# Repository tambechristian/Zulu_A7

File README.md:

# Zulu A7

Zulu A7 is a USB FPGA board built around an AMD/Xilinx Artix-7
XC7A35T-2CPG236I. An FTDI FT2232HL bridge provides JTAG (channel A) and a
UART (channel B) over one micro-USB port. The board carries 64 MB of SDRAM,
a 128 Mbit quad-SPI configuration flash, a microSD socket, a Pmod host
header and a 40-pin breadboard header. It runs from USB through a
single-cell LiPo charger with power path and three buck regulators (3.3 V,
1.8 V and 1.0 V). The PCB is a 69.85 x 25.40 mm, six-layer HDI board.

The main design is the Altium Designer project in `Zulu_Altium_VS_Code/`.
Its fabrication and turnkey-assembly packages for PCBWay are dated
2026-10-07. Build and test results are not recorded in this repository.

## Origin and attribution

Zulu A7 is an adaptation of **XuLA2**, the USB FPGA prototyping board by
Dave Vandenbout / XESS Corp. (copyright 2012 XESS Corp.), published at
<https://github.com/xesscorp/XuLA2>. Its hardware design (schematic and
layout in `pcb/`) is licensed under
[CC BY-SA 3.0 Unported](https://creativecommons.org/licenses/by-sa/3.0/),
per the notice on its schematic. This repository does
not imply any connection with, or endorsement by, XESS Corp. or Dave
Vandenbout.

XESS's [product listing](https://www.tindie.com/products/xesscorp/xula2-lx25-fpga-prototyping-board/)
says the whole XuLA2 design was made open source and that anyone who
re-designs it must open-source their design too. As of 2026-10-07 it lists
XuLA2 as retired. The licence terms are those of CC BY-SA 3.0.

XuLA2 (schematic version 2.0, EAGLE 5 files) had a Xilinx Spartan-6
XC6SLX25 in FT256 and a Microchip PIC18F14K50 that handled reset and
initialisation, clock generation and USB-to-JTAG. It also had 256 Mbit
SDRAM, 8 Mbit SPI flash, a microSD socket, a mini-USB connector, ZLDO1117
3.3 V and 1.2 V regulators, a 40-pin breadboard prototyping header and an
aux JTAG header.

### Lineage

1. **XuLA2**: XESS Corp., 2012. The upstream design.
2. **XuLA3**: Christian Tambe's own rework of XuLA2, started 2026-08-10 in a
   separate local repository that is not published. It is not an XESS
   design. Its baseline is the XuLA2 schematic in EAGLE XML. The move to the
   Artix-7, the FT2232H bridge and an LTC3569 triple buck was made in XuLA3,
   before the fork. There the `xess` library was renamed `ctambe`, and the
   schematic AUTHOR and copyright line were changed to Christian Tambe.
3. **Zulu A7**: forked from XuLA3 on 2026-08-29 (commit `30a0e65`, "Zulu A7
   forks from XuLA3: the board is renamed, not redesigned"). That commit
   renamed X2's package XULA-DIP37 to ZULU-DIP37 and its deviceset XULA-CONN
   to ZULU-CONN, dropped unused devicesets including XC6SLX25-FT256 and
   PIC18F14K50, and set the version to 1.0. `zulu_a7.brd` took only its
   layer, settings and autorouter sections from the XuLA3 board;
   `tools/make_board.py` writes the geometry new.
4. **Altium and KiCad copies**: the EAGLE schematic was imported into Altium
   with the EAGLE Import Wizard in `Zulu_Altrium/` (commit `6d2efd6`).
   `Zulu_Altium_VS_Code/` is a later working copy of that project. The SC189
   regulators, the BQ24232 charger and the X2 pin field are Altium-side
   changes, and the board was routed there. `Zulu_kicad/` is a KiCad
   conversion of the Altium project.

### Main changes from XuLA2

| | XuLA2 | Zulu A7 |
|---|---|---|
| FPGA | Xilinx Spartan-6 XC6SLX25, FT256 | AMD/Xilinx Artix-7 XC7A35T-2CPG236I |
| USB bridge | Microchip PIC18F14K50 | FTDI FT2232HL with a 93LC46B EEPROM |
| USB connector | Hirose UX60SC-MB-5ST mini-USB | Molex 105017-0001 micro-USB |
| SDRAM | W9825G6JH-5, 256 Mbit | Alliance AS4C32M16SB-7TCN, 512 Mbit |
| Flash | W25Q80BV, 8 Mbit | Winbond W25Q128JV, 128 Mbit quad SPI |
| microSD | ALPS SCHD3A0100 | Hirose DM3D-SF |
| Clock | generated by the PIC18F14K50 | 12.000 MHz oscillator shared by the FT2232HL and the FPGA |
| Power | ZLDO1117 3.3 V and 1.2 V regulators | BQ24232 LiPo charger and three SC189 bucks (3.3 / 1.8 / 1.0 V) |
| Headers | 40-pin breadboard header, aux JTAG header | 40-pin breadboard header X2 with its own pin map, 2x6 Pmod host header J1, unpopulated JTAG holes JP3/JP4 |
| PCB | 2 in x 1 in | 69.85 x 25.40 mm, six-layer HDI |

XuLA3 and the EAGLE-era Zulu A7 used an LTC3569 triple buck. The Altium
copy replaced it on 2026-09-06 with the three SC189 bucks, so the EAGLE
files in this repository still show the LTC3569.

`docs/Zulu_A7-Design-Change-Record.html` lists the part changes from the
fork. Its "Was" column is the XuLA3 rev 1 state, which is mostly but not
entirely the XuLA2-LX25 BOM (the ESP8266 header and the BTN1 PTA-142 button
were XuLA3 additions). It predates the SC189 power section.

### What still comes from XuLA2

Compared with the `xess` library of the XuLA2 schematic (in its EAGLE XML
form), the `ctambe` library in the root `zulu_a7.sch` keeps 16 packages
byte-identical (for example TSOPII-54, SCHD3A0100, UX60SC-MB-5ST, CC_BY,
CC_CC and CC_COPYRIGHT), and 7 symbols and 5 devicesets are identical. The
later EAGLE copies keep the same packages with their keepout outlines
removed. Sheet text such as "Block Diagram",
"PROTOTYPING HEADER", "FPGA Connections" and the three licence lines is
kept verbatim. This material is in the EAGLE files (`zulu_a7.sch`,
`zulu_a7.brd` and the EAGLE copies in `Claude_Fable/`, `Zulu_Altrium/`,
`Zulu_Altium_VS_Code/` and `Altium_backup/`), in the SchDoc, PcbLib and
PcbDoc files of the four Altium copies and the September schematic PDFs,
and in `Zulu_kicad/kicad_project/` (`ctambe.kicad_sym`, footprints in
`zulu_a7.pretty/`, `zulu_a7.kicad_pcb` and `zulu_a7_2.kicad_sch`).

### Notices

In every copy of the schematic, the General IO sheet (sheet 3 of 7 in EAGLE
and Altium, `zulu_a7_2.SchDoc`; page 4 of 8 in KiCad, `zulu_a7_2.kicad_sch`,
under the added root sheet) carries "2026, Christian Tambe. Some rights
reserved." and the three CC BY-SA Unported licence lines, beside the CC
logos. The title block of every sheet reads "AUTHOR: Christian Tambe": in the
EAGLE files through the AUTHOR attribute, and in the Altium copies
(`Zulu_Altium_VS_Code/`, `Zulu_Altium_VS_Code_HDI_Optimized/`) and the KiCad
copy since 2026-10-08 (`Zulu_Altium_VS_Code/docs/schematic_author.md`). The
superseded `Zulu_Altrium/` and the `Altium_backup/` snapshot still show the
importer's placeholder "AUTHOR".
The upstream line "2012, XESS Corp. Some rights reserved." and the upstream
AUTHOR "Dave Vandenbout / XESS Corp." were replaced during the XuLA3 rework
and have never been in this repository's history, and the sheets do not yet
carry the XESS line again.
[LICENSE](LICENSE) reproduces the upstream notice and gives the credit for
XuLA2; keep it with any copy of the schematics.

## Board facts

- **FPGA**: U1 XC7A35T-2CPG236I, CPG236 BGA, 10 x 10 mm, 0.5 mm pitch.
- **USB**: U2 FTDI FT2232HL (LQFP-64). Channel A is MPSSE JTAG plus
  PROG#/DONE, channel B is the UART. U10 93LC46B configuration EEPROM.
  X1 Molex 105017-0001 micro-USB-B.
- **Memory**: U3 Alliance Memory AS4C32M16SB-7TCN, 512 Mbit (64 MB) SDRAM;
  the memory controller must use 10 column bits (A0-A9). U4 Winbond
  W25Q128JVSIQ, 128 Mbit quad SPI; the 17,536,096-bit bitstream leaves about
  14 MB for user data.
- **Clock**: Q1 ECS-3225SMV-120-FP-TR, 12.000 MHz, +-10 ppm HCMOS
  oscillator, driving the FT2232HL and the FPGA through 33 ohm each.
- **Power**: U8 TI BQ24232 single-cell LiPo charger with power path. Its
  output VU, the system rail that feeds the three bucks, is 4.4 V from USB
  and VBAT - 60 mV on battery; 495 mA input limit, 244 mA charge current.
  Battery on X4, a JST PH 2-pin header (pin 1 = battery +); the BOM has no
  battery. U5, U6 and U7 are Semtech SC189 bucks for 3.3 V, 1.8 V and 1.0 V
  (FPGA core).
- **I/O**: X2 40-pin breadboard header, 2.54 mm pitch, rows 22.86 mm apart,
  mounted from the underside; GND on pins 1, 17 and 21, +3.3 V on 18,
  +1.8 V on 19, +1.0 V on 20, VU on 22. J1 2x6 Pmod host header. X3 Hirose
  DM3D-SF microSD socket with card detect. JP3/JP4 unpopulated 1x3 JTAG
  holes. User button BTN, RGB LED LD0 and five 0603 LEDs (LD1-LD5).
- **PCB**: 69.85 x 25.40 mm, six layers (Top / L2 GND / L3 / L4 / L5 VCC3V3 /
  Bottom). Two-step HDI 1+1+N+1+1 with 0.15 mm laser microvias, 0.15 mm
  L3-L4 buried vias and 0.20 mm through vias. 3.0 / 3.5 mil minimum
  track / space. USB pair 90 ohm differential.
- **Status**: fully routed. Altium DRC on the final saved board (2026-10-07
  16:53) reports 0 violations; the report is
  `Zulu_Altium_VS_Code/Imported zulu_a7.PrjPcb/Design Rule Check - zulu_a7.drc`.
  The release packages identify the board by its PcbDoc SHA-256,
  `89a421b9060195d66bed82f7a4e7d80121bd0e9d679a3fee32289e8f541f4bde`.
- **Assembly**: 172 fitted designators (32 top, 140 bottom), 76 parts in
  0201. ENIG finish recommended. No fiducials on the board.

Known caveats, from `Zulu_Altium_VS_Code/docs/power_budget.md` and the
assembly notes:

- The worst-case draw (about 697 mA) exceeds the 495 mA input limit and needs
  the battery; with no battery the board browns out at that load. The board
  draws more than 100 mA before the FT2232HL enumerates.
- Every rail has more output capacitance than the SC189 datasheet's 30 uF
  start-up limit. Scope the three rails at power-on on the first board.
- LD0 green and blue are sunk from 3.3 V through 33 ohm and may be dim or
  dark; only red has margin.
- U5 and U7 look alike; swapping them puts 3.3 V on the FPGA core.

## Repository layout

| Entry | Status | Contents |
|---|---|---|
| `Zulu_Altium_VS_Code/` | **Current, authoritative** | Main Altium project: `Imported zulu_a7.PrjPcb/` (7 SchDocs, PcbDoc, PcbLib, released Gerber and NC-drill files, DRC report), `fabrication/`, `assembly/`, `docs/` (stage and decision records), `tools/`, `board/` (outline DXF; `JLCPCB-HDI-ENQUIRY.md` is superseded). The Stage-13 route plan is `tools/stage13/plan.json`; the root `plan.json` is a small XADC-knot plan. Its root `zulu_a7.sch` is the stale EAGLE import source. |
| `Zulu_Altium_VS_Code_HDI_Optimized/` | Derivative | Same-outline copy of the main board with 13 HDI sites turned into through vias, with its own fab zips and assembly release. |
| `Zulu_kicad/` | Derivative | KiCad 10 conversion of the main project, netlist-proven. Design rules were not translated, so KiCad DRC is not meaningful; do not refill zones. Altium stays the fabrication master. |
| `Zulu_Altrium/` | Superseded | Earlier Altium working copy: the EAGLE import, the September schematic work, routing placed through Stage 8 and the Stage 9-12 records (plans, never placed). Its PcbDoc is an intermediate Stage-13 Phase II board. |
| `Altium_backup/` | Snapshot | Backup of the Altium project taken during the September routing stages. |
| `Claude_Fable/` | Legacy | EAGLE/Fusion-era 8-layer HDI working copy, its board variants and tools. |
| `zulu_a7.sch` | Legacy | EAGLE schematic from the fork. It predates the released design (no BQ24232, no SC189) and is not the Altium import source, which is the later `Zulu_Altrium/zulu_a7.sch`. |
| `zulu_a7.brd` | Legacy | EAGLE board from the fork. |
| `tools/` | Legacy | EAGLE-era Python tools that read or write the root `zulu_a7.sch` / `zulu_a7.brd` (for example `make_board.py`, `validate.py`, `change_record.py`). |
| `board/` | Legacy | EAGLE/Fusion-era fab planning: `STACKUP.md`, EAGLE `.dru` rule files, DFM enquiry drafts, `pcbway/README.md`. Superseded by `Zulu_Altium_VS_Code/fabrication/PCBWAY_FAB_NOTES.txt`. |
| `docs/` | Mixed | `zulu_a7-bom.csv` is the current master BOM. `Zulu_A7-Design-Change-Record.html` is an EAGLE-era record. |
| `vivado/` | Mixed | `zulu_a7_pins.xdc` is current (Stage-13 pin permutation). `zulu_a7_io.rpt`, `zulu_a7_io.csv` and `zulu_a7_clocks.rpt` come from the 2026-09-10 Vivado run and show pre-swap balls; `zulu_a7_top.v` is the HDL top module used for that run. |
| `Zulu A7 Board Plan.html` | Legacy | Generated by `tools/board_plan.py`; shows the old 60.96 x 25.40 mm board. |
| `fix_sheet_names.cmd` | Legacy | EAGLE-era helper, run after exporting `zulu_a7.sch` from Fusion. |
| `W*P1.pdf`, `W*P2.pdf` | Vendor documents | PCBWay order-page printouts. They are not the fabrication spec; see `PCBWAY_FAB_NOTES.txt`. |
| `.gitignore` | | Ignores EAGLE and Vivado scratch files, `Datasheet/`, `board/*.pdf` and `archives/`. |

`archives/` and `Datasheet/` are ignored and are not part of the repository.

## Where to start

1. Open `Zulu_Altium_VS_Code/Imported zulu_a7.PrjPcb/zulu_a7.PrjPcb` in
   Altium Designer. The folder name comes from the EAGLE Import Wizard.
2. `Zulu_Altium_VS_Code/fabrication/PCBWAY_FAB_NOTES.txt`: what the current
   board is (stack, vias, impedance, outline, file map, final DRC).
3. `Zulu_Altium_VS_Code/assembly/Zulu_A7_Assembly_Notes.txt` and
   `Zulu_Altium_VS_Code/docs/pcbway_assembly_release.md`: the assembly
   release. To regenerate it, run
   `python tools/generate_jlcpcb_assembly.py --release-date 2026-10-07` from
   `Zulu_Altium_VS_Code/`.
4. `docs/zulu_a7-bom.csv`: the master BOM. Regenerate it only with
   `Zulu_Altium_VS_Code/tools/master_bom.py`; the copies in `Zulu_Altrium/`
   and `Altium_backup/` read stale sheets.
5. `Zulu_Altium_VS_Code/docs/power_budget.md`: power path, current budget
   and the caveats above.
   `Zulu_Altium_VS_Code/docs/stackup_impedance.md` gives the layer stack and the
   impedance of every routed trace width (`tools/stackup_impedance.py`).
6. `Zulu_Altium_VS_Code/docs/stage13_route_plan.md`, section "Final
   implementation closeout": how routing was finished. Later board changes
   are in `x1_slot_fix.md`, `x2_power_pins.md`, `x2_pin_labels.md` and
   `btn_move.md` in the same folder.
7. For FPGA work: `vivado/zulu_a7_pins.xdc` is the current pin map (the
   SDRAM ports need DRIVE 8, as set there). This repository has no
   programming instructions, FT2232H EEPROM image or example bitstream.
8. `Zulu_Altium_VS_Code_HDI_Optimized/HDI_OPTIMIZATION_NOTES.md` (the
   derivative board) and `Zulu_kicad/CONVERSION.md` (the KiCad copy).

Notes:

- No current schematic PDF is tracked. The `zulu_a7.pdf` files in
  `Zulu_Altrium/` and `Altium_backup/` are 2026-09-10 prints and are out of
  date.
- `Zulu_Altium_VS_Code/docs/` is a dated record of stages and decisions, and
  older entries describe superseded states. For example,
  `Zulu_Altium_VS_Code/docs/hdi_spec.md` and `board/pcbway/README.md` name
  JLCPCB as the fab. Where they disagree with the release files, the release
  files are current.
- `Zulu_Altium_VS_Code/tools/README.md` covers the import, schematic-edit and
  audit scripts (`pip install olefile pywin32`). It does not cover the
  routing toolkits or the assembly generator, which also needs `pymupdf` and
  `altium-monkey` (`pip install olefile pymupdf altium-monkey`).
- Vendor datasheets are not tracked. After a fresh clone, put AMD's package
  pinout file for the XC7A35T-CPG236 back as
  `Datasheet/xc7a35tcpg236pkg_pinout.txt`. Without it, `tools/validate.py`,
  `tools/vivado_io_check.py`, `tools/escape/rings.py` and
  `tools/change_record.py`, and the Altium copy's `tools/bom_audit.py`,
  `tools/connectivity_check.py` and `tools/stage13/xdc_check.py`, lose their
  ball checks or fail.

## Licence

See [LICENSE](LICENSE). Except for the third-party material listed there,
this repository, scripts included, is licensed under
[CC BY-SA 3.0 Unported](https://creativecommons.org/licenses/by-sa/3.0/legalcode).
It is an adaptation of XuLA2 (see above). Under section 8(b) of the licence,
XESS Corp., as Licensor of XuLA2, offers each recipient a licence to the
original XuLA2 Work on the same terms.

Design references, not files: some circuit choices follow Digilent's Cmod
A7. The SC189 bucks are "Cmod A7 style", the XADC input network is the one
Digilent uses on the Cmod A7, and the SDRAM, microSD and GPIO ball
assignments were first checked against the Cmod A7-35T. No Digilent file is
in this repository, and this licence grants nothing on Digilent's behalf.

Not in this repository: XuLA2's firmware (XESS code under GPL v2 or later,
plus Microchip USB-stack files under Microchip's licence), its FPGA example
designs (many files under GPL or LGPL), and the vendor datasheets and the
AMD/Xilinx pinout file (`Datasheet/` is ignored).

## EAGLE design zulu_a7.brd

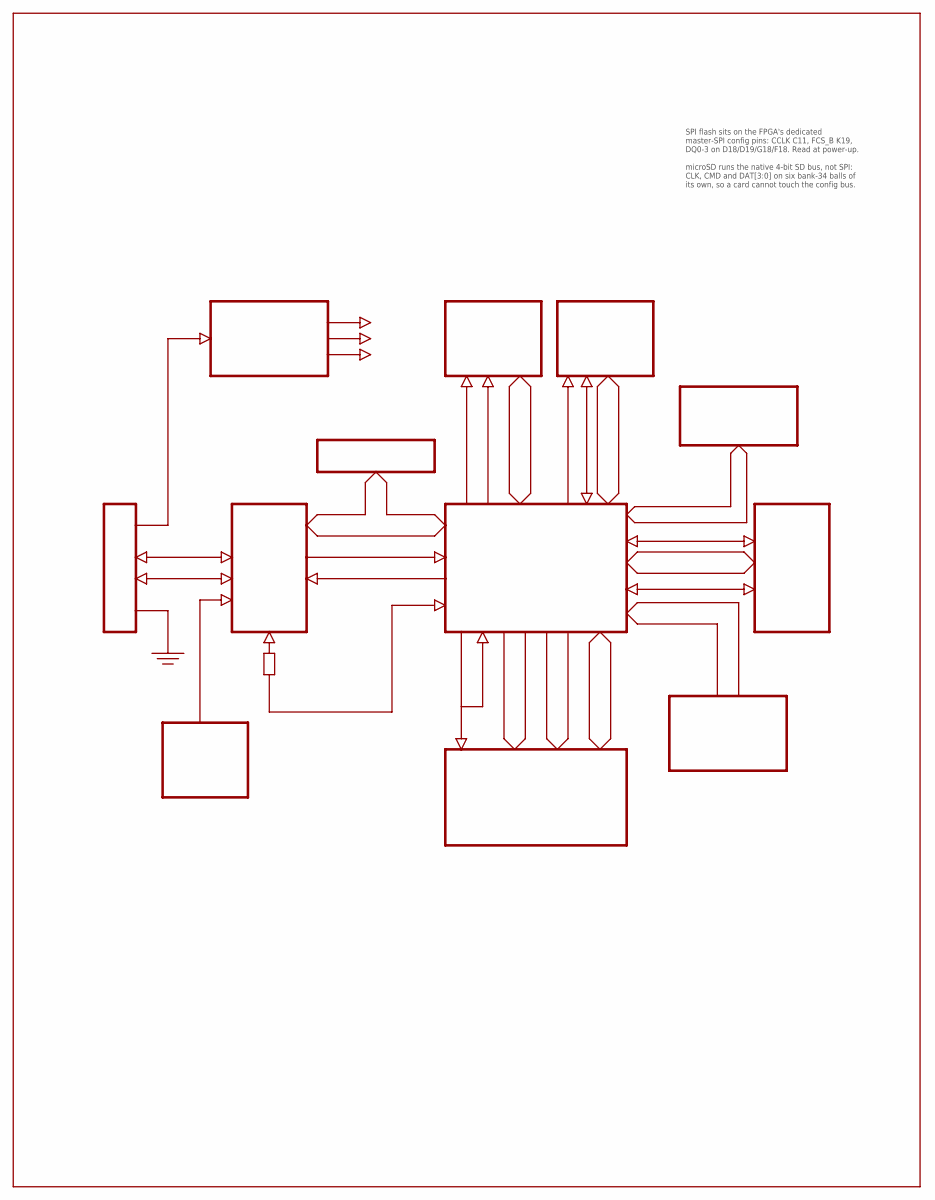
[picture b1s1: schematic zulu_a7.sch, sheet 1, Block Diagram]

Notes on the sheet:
SPI flash sits on the FPGA's dedicated master-SPI config pins: CCLK C11, FCS_B K19, DQ0-3 on D18/D19/G18/F18. Read at power-up. microSD runs the native 4-bit SD bus, not SPI: CLK, CMD and DAT[3:0] on six bank-34 balls of its own, so a card cannot touch the config bus.

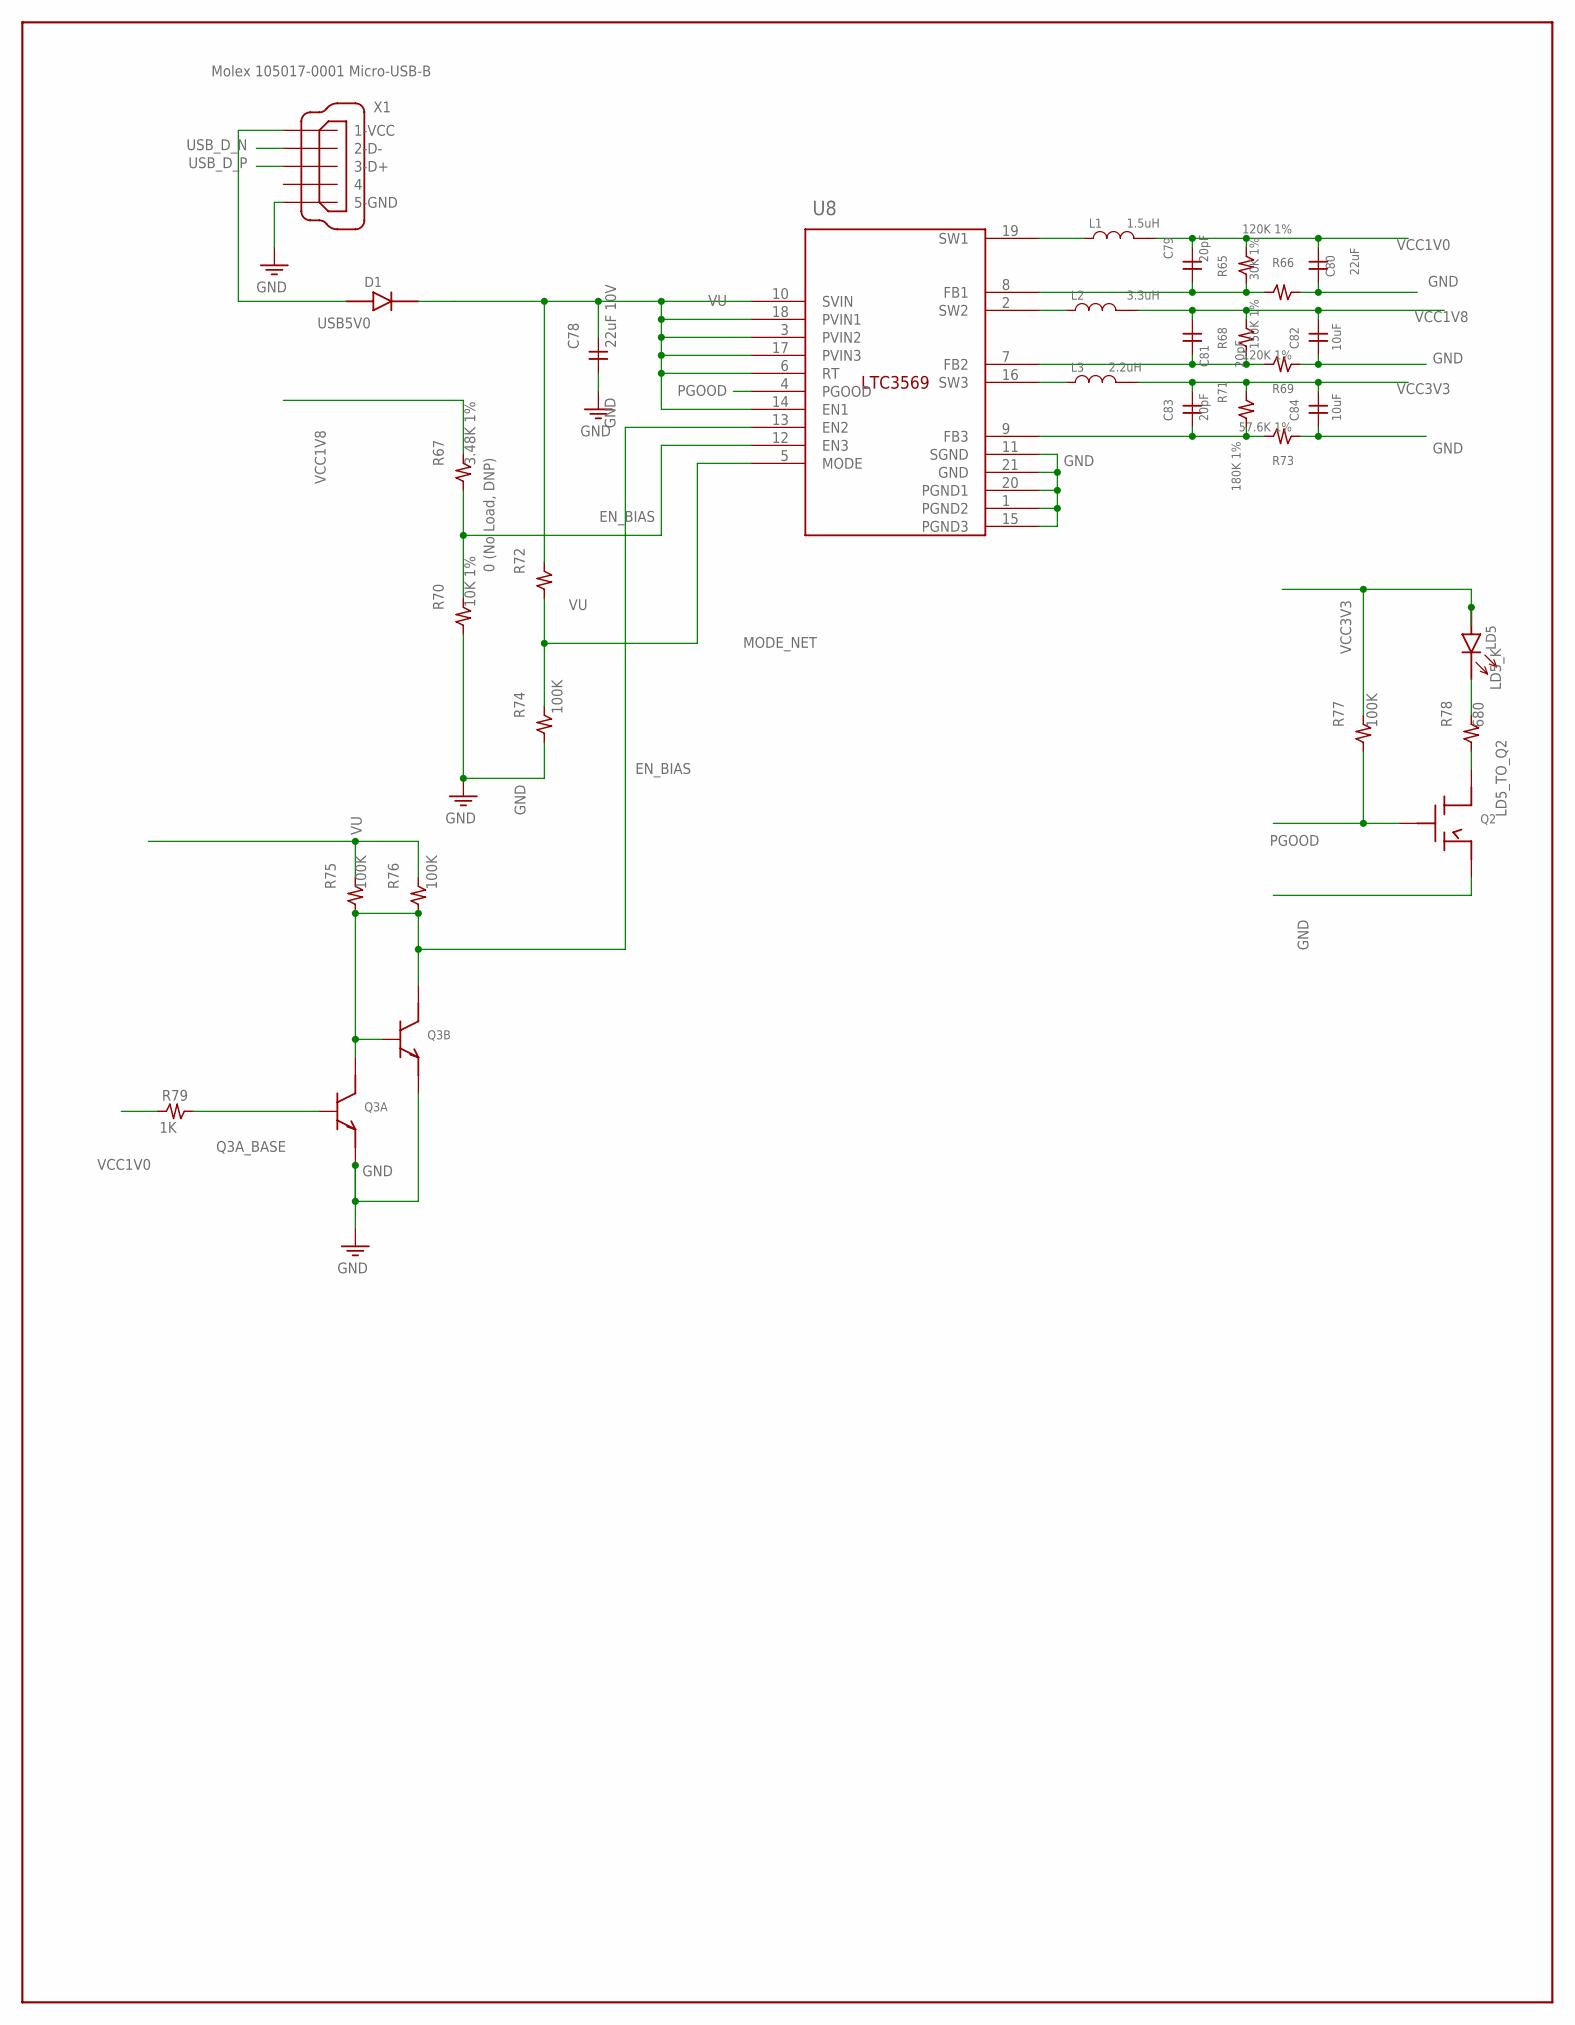
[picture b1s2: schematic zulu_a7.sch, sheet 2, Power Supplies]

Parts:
C78: 22uF 10V; C0805
C79, C81, C83: 20pF; C0402
C80: 22uF; C0805
C82, C84: 10uF; C0603
D1: PMEG2020EJ,115; SOD123
L1: 1.5uH; IND2520
L2: 3.3uH; IND2520
L3: 2.2uH; IND2520
LD5: green; LED0603
Q2: 2N7002; SOT23-3
Q3: MBT3904DW1T1; SOT363
R65: 30K 1%; R0402
R66, R69: 120K 1%; R0402
R67: 3.48K 1%; R0402
R68: 150K 1%; R0402
R70: 10K 1%; R0402
R71: 180K 1%; R0402
R72: 0 (No Load, DNP); R0402
R73: 57.6K 1%; R0402
R74, R75, R76, R77: 100K; R0402
R78: 680; R0402
R79: 1K; R0402
U8: LTC3569EUDC#TRPBF; LTC3569-QFN20
X1: Molex 105017-0001 Micro-USB-B; MOLEX-105017-0001

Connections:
EN_BIAS: Q3.4 (B), Q3.5 (C), Q3.6 (C), R67.1, R70.2, R75.1, R76.1, U8.12 (EN3), U8.13 (EN2)
FB1_NODE: C79.1, R65.1, R66.2, U8.8 (FB1)
FB2_NODE: C81.1, R68.1, R69.2, U8.7 (FB2)
FB3_NODE: C83.1, R71.1, R73.2, U8.9 (FB3)
GND: C78.1, C80.1, C82.1, C84.1, Q2.S, Q3.2 (E), Q3.3 (E), R66.1, R69.1, R70.1, R73.1, R74.1, U8.1 (PGND2), U8.11 (SGND), U8.15 (PGND3), U8.20 (PGND1), U8.21 (GND), X1.5 (5-GND), X1.MH1 (5-GND), X1.MH2 (5-GND), X1.MP1 (5-GND), X1.MP2 (5-GND), X1.MP3 (5-GND), X1.MP4 (5-GND), X1.MS1 (5-GND), X1.MS2 (5-GND); also elsewhere on the board
LD5_K: LD5.K, R78.2
LD5_TO_Q2: Q2.D, R78.1
MODE_NET: R72.1, R74.2, U8.5 (MODE)
PGOOD: Q2.G, R77.1, U8.4 (PGOOD)
Q3A_BASE: Q3.1 (B), R79.2
SW1_NET: L1.1, U8.19 (SW1)
SW2_NET: L2.1, U8.2 (SW2)
SW3_NET: L3.1, U8.16 (SW3)
USB5V0: D1.A, X1.1 (1-VCC)
USB_D_N: X1.2 (2-D-); also elsewhere on the board
USB_D_P: X1.3 (3-D+); also elsewhere on the board
VCC1V0: C79.2, C80.2, L1.2, R65.2, R79.1; also elsewhere on the board
VCC1V8: C81.2, C82.2, L2.2, R67.2, R68.2; also elsewhere on the board
VCC3V3: C83.2, C84.2, L3.2, LD5.A, R71.2, R77.2; also elsewhere on the board
VU: C78.2, D1.K, R72.2, R75.2, R76.2, U8.3 (PVIN2), U8.6 (RT), U8.10 (SVIN), U8.14 (EN1), U8.17 (PVIN3), U8.18 (PVIN1); also elsewhere on the board

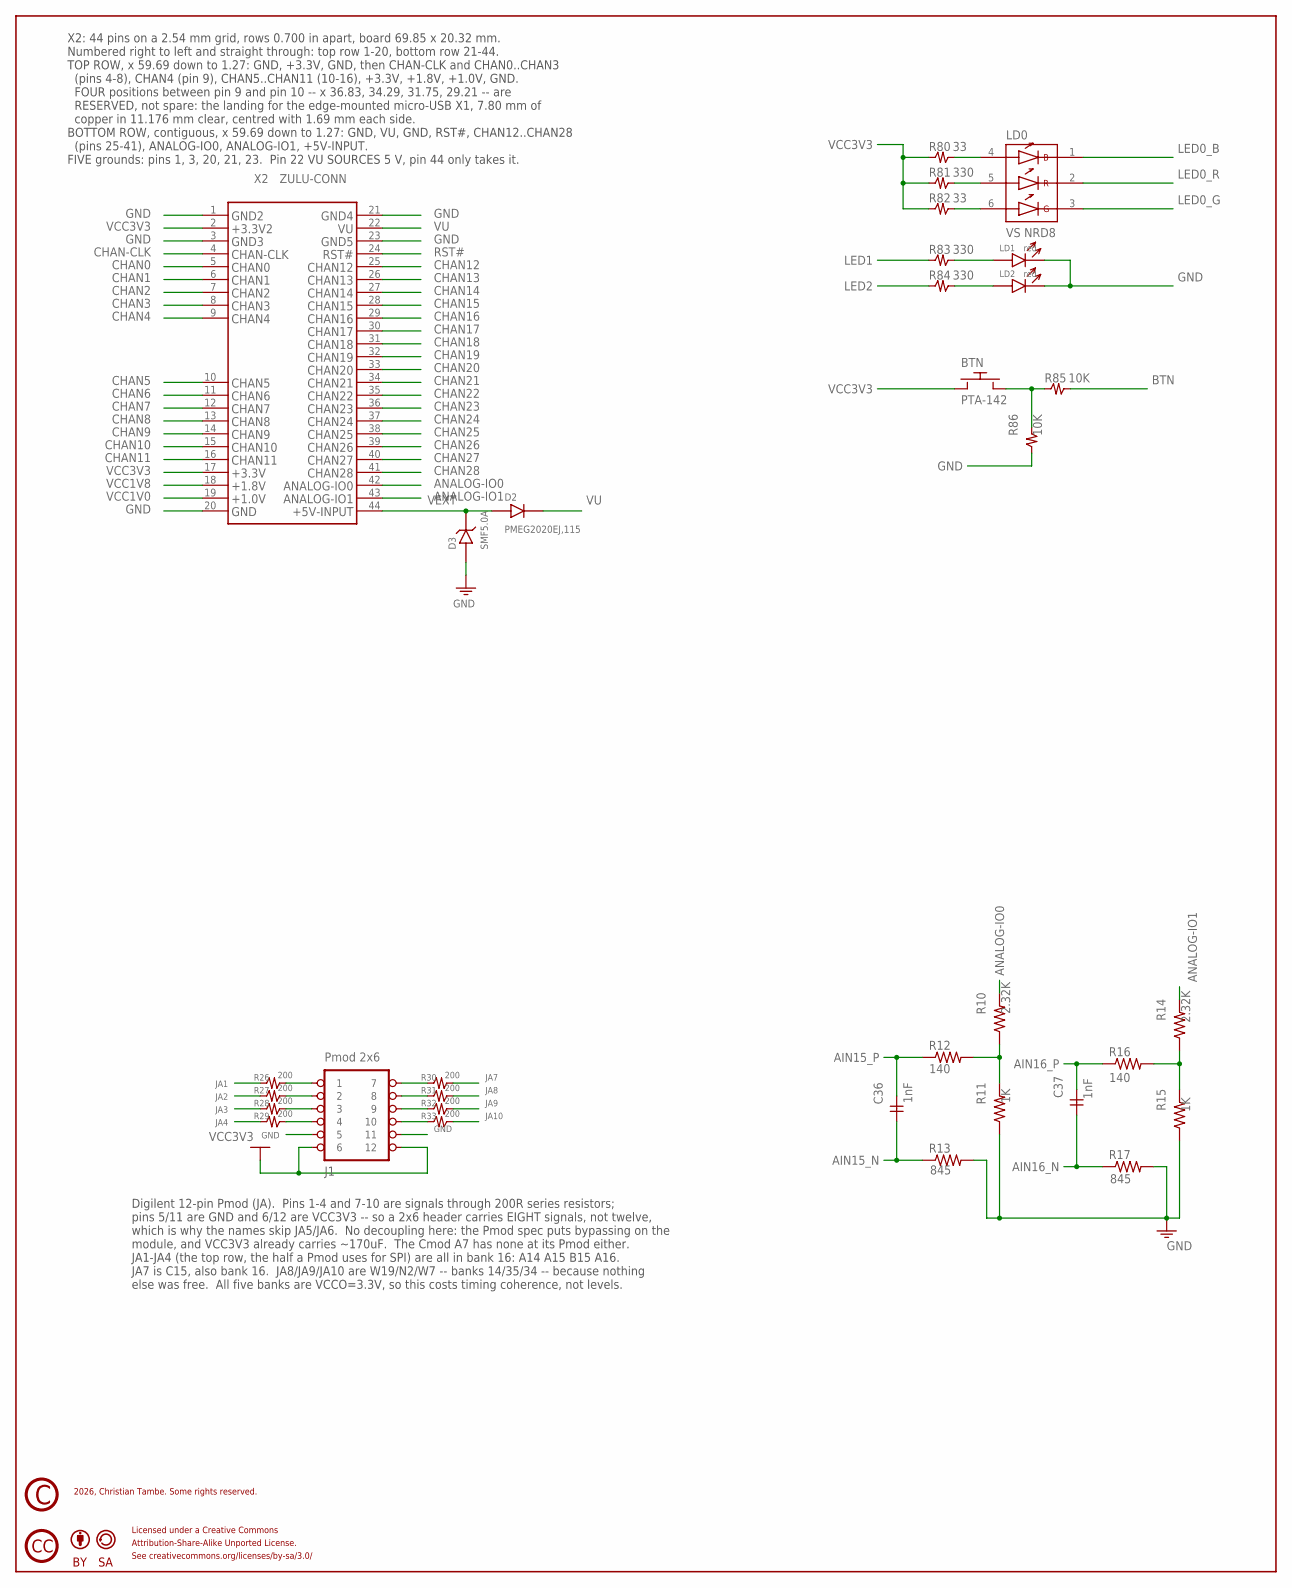
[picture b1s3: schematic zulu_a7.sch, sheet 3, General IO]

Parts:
BTN: PTA-142
C36, C37: 1nF; C0402
D2: PMEG2020EJ,115; SOD123
D3: SMF5.0A; SOD123
J1: Pmod 2x6; 2X06
LD0: VS NRD8; VS-NRD8
LD1, LD2: red; LED0603
R10, R14: 2.32K; R0201
R11, R15: 1K; R0201
R12, R16: 140; R0201
R13, R17: 845; R0201
R26, R27, R28, R29, R30, R31, R32, R33: 200; R0201
R80, R82: 33; R0402
R81, R83, R84: 330; R0402
R85, R86: 10K; R0402
U$2: CC_CC
U$3: CC_BY
U$4: CC_SA
U$5: CC_COPYRIGHT
X2: ZULU-CONN; ZULU-DIP37

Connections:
AIN15_N: C36.1, R13.1; also elsewhere on the board
AIN15_P: C36.2, R12.1; also elsewhere on the board
AIN16_N: C37.1, R17.1; also elsewhere on the board
AIN16_P: C37.2, R16.1; also elsewhere on the board
ANALOG-IO0: R10.2, X2.42
ANALOG-IO1: R14.2, X2.43
BTN: R85.2; also elsewhere on the board
CHAN0: X2.5; also elsewhere on the board
CHAN1: X2.6; also elsewhere on the board
CHAN2: X2.7; also elsewhere on the board
CHAN3: X2.8; also elsewhere on the board
CHAN4: X2.9; also elsewhere on the board
CHAN5: X2.10; also elsewhere on the board
CHAN6: X2.11; also elsewhere on the board
CHAN7: X2.12; also elsewhere on the board
CHAN8: X2.13; also elsewhere on the board
CHAN9: X2.14; also elsewhere on the board
CHAN10: X2.15; also elsewhere on the board
CHAN11: X2.16; also elsewhere on the board
CHAN12: X2.25; also elsewhere on the board
CHAN13: X2.26; also elsewhere on the board
CHAN14: X2.27; also elsewhere on the board
CHAN15: X2.28; also elsewhere on the board
CHAN16: X2.29; also elsewhere on the board
CHAN17: X2.30; also elsewhere on the board
CHAN18: X2.31; also elsewhere on the board
CHAN19: X2.32; also elsewhere on the board
CHAN20: X2.33; also elsewhere on the board
CHAN21: X2.34; also elsewhere on the board
CHAN22: X2.35; also elsewhere on the board
CHAN23: X2.36; also elsewhere on the board
CHAN24: X2.37; also elsewhere on the board
CHAN25: X2.38; also elsewhere on the board
CHAN26: X2.39; also elsewhere on the board
CHAN27: X2.40; also elsewhere on the board
CHAN28: X2.41; also elsewhere on the board
CHAN-CLK: X2.4; also elsewhere on the board
GND: D3.A, J1.5, J1.11, LD1.K, LD2.K, R11.1, R13.2, R15.1, R17.2, R86.1, X2.1, X2.3, X2.20, X2.21, X2.23; also elsewhere on the board
JA1: R26.1; also elsewhere on the board
JA2: R27.1; also elsewhere on the board
JA3: R28.1; also elsewhere on the board
JA4: R29.1; also elsewhere on the board
JA7: R30.2; also elsewhere on the board
JA8: R31.2; also elsewhere on the board
JA9: R32.2; also elsewhere on the board
JA10: R33.2; also elsewhere on the board
LED0_B: LD0.1; also elsewhere on the board
LED0_G: LD0.3; also elsewhere on the board
LED0_R: LD0.2; also elsewhere on the board
LED1: R83.1; also elsewhere on the board
LED2: R84.1; also elsewhere on the board
N$BTN: BTN.3 (2), BTN.4 (2), R85.1, R86.2
N$LD0B: LD0.4, R80.2
N$LD0G: LD0.6, R82.2
N$LD0R: LD0.5, R81.2
N$LD1A: LD1.A, R83.2
N$LD2A: LD2.A, R84.2
NODE_P0: R10.1, R11.2, R12.2
NODE_P1: R14.1, R15.2, R16.2
PMOD-1: J1.1, R26.2
PMOD-2: J1.2, R27.2
PMOD-3: J1.3, R28.2
PMOD-4: J1.4, R29.2
PMOD-7: J1.7, R30.1
PMOD-8: J1.8, R31.1
PMOD-9: J1.9, R32.1
PMOD-10: J1.10, R33.1
RST#: X2.24; also elsewhere on the board
VCC1V0: X2.19; also elsewhere on the board
VCC1V8: X2.18; also elsewhere on the board
VCC3V3: BTN.1, BTN.2 (1), J1.6, J1.12, R80.1, R81.1, R82.1, X2.2, X2.17; also elsewhere on the board
VEXT: D2.A, D3.K, X2.44
VU: D2.K, X2.22; also elsewhere on the board

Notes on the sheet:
2026, Christian Tambe. Some rights reserved.
Licensed under a Creative Commons
Attribution-Share-Alike Unported License.
See creativecommons.org/licenses/by-sa/3.0/
Digilent 12-pin Pmod (JA). Pins 1-4 and 7-10 are signals through 200R series resistors; pins 5/11 are GND and 6/12 are VCC3V3 -- so a 2x6 header carries EIGHT signals, not twelve, which is why the names skip JA5/JA6. No decoupling here: the Pmod spec puts bypassing on the module, and VCC3V3 already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
X2: 44 pins on a 2.54 mm grid, rows 0.700 in apart, board 69.85 x 20.32 mm. Numbered right to left and straight through: top row 1-20, bottom row 21-44. TOP ROW, x 59.69 down to 1.27: GND, +3.3V, GND, then CHAN-CLK and CHAN0..CHAN3 (pins 4-8), CHAN4 (pin 9), CHAN5..CHAN11 (10-16), +3.3V, +1.8V, +1.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

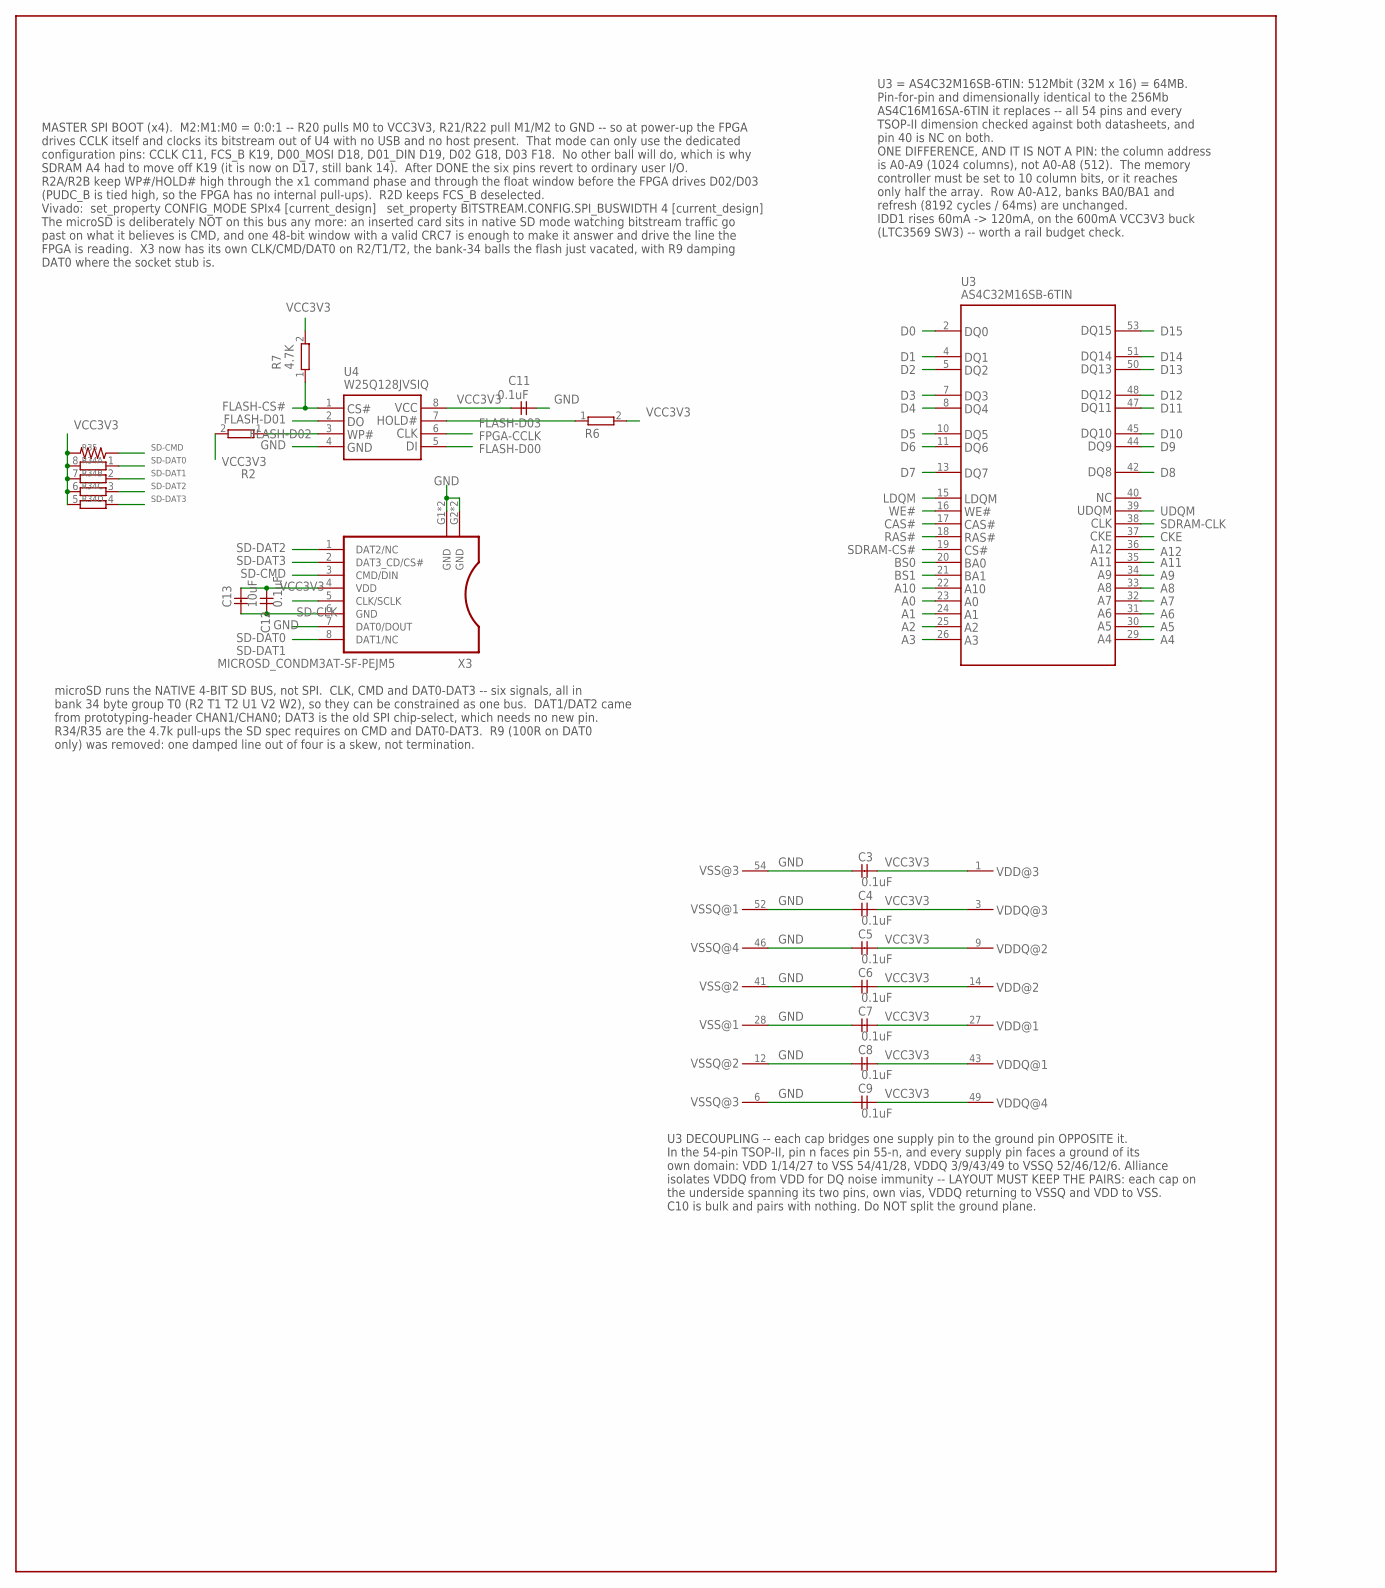
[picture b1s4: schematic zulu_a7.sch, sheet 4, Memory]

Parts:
C3, C4, C5, C6, C7, C8, C9, C11, C12: 0.1uF; C0402
C13: 10uF; C0603
R2, R6, R7: 4.7K; R0201
R34: 4.7K; 742C083
R35: 4.7K; R0402
U3: AS4C32M16SB-6TIN; TSOPII-54
U4: W25Q128JVSIQ; SOIC-8_208MIL; DIGIKEY# W25Q128JVSIQ-ND
X3: MICROSD_CONDM3AT-SF-PEJM5; DM3AT-SF-PEJM5

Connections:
A0: U3.23; also elsewhere on the board
A1: U3.24; also elsewhere on the board
A2: U3.25; also elsewhere on the board
A3: U3.26; also elsewhere on the board
A4: U3.29; also elsewhere on the board
A5: U3.30; also elsewhere on the board
A6: U3.31; also elsewhere on the board
A7: U3.32; also elsewhere on the board
A8: U3.33; also elsewhere on the board
A9: U3.34; also elsewhere on the board
A10: U3.22; also elsewhere on the board
A11: U3.35; also elsewhere on the board
A12: U3.36; also elsewhere on the board
BS0: U3.20; also elsewhere on the board
BS1: U3.21; also elsewhere on the board
CAS#: U3.17; also elsewhere on the board
CKE: U3.37; also elsewhere on the board
D0: U3.2; also elsewhere on the board
D1: U3.4; also elsewhere on the board
D2: U3.5; also elsewhere on the board
D3: U3.7; also elsewhere on the board
D4: U3.8; also elsewhere on the board
D5: U3.10; also elsewhere on the board
D6: U3.11; also elsewhere on the board
D7: U3.13; also elsewhere on the board
D8: U3.42; also elsewhere on the board
D9: U3.44; also elsewhere on the board
D10: U3.45; also elsewhere on the board
D11: U3.47; also elsewhere on the board
D12: U3.48; also elsewhere on the board
D13: U3.50; also elsewhere on the board
D14: U3.51; also elsewhere on the board
D15: U3.53; also elsewhere on the board
FLASH-CS#: R7.1, U4.1; also elsewhere on the board
FLASH-D00: U4.5; also elsewhere on the board
FLASH-D01: U4.2; also elsewhere on the board
FLASH-D02: R2.1, U4.3; also elsewhere on the board
FLASH-D03: R6.1, U4.7; also elsewhere on the board
FPGA-CCLK: U4.6; also elsewhere on the board
GND: C3.1, C4.1, C5.1, C6.1, C7.1, C8.1, C9.1, C11.1, C12.1, C13.1, U3.6, U3.12, U3.28, U3.41, U3.46, U3.52, U3.54, U4.4, X3.6 (GND), X3.G1 (GND), X3.G2 (GND), X3.G3 (GND), X3.G4 (GND); also elsewhere on the board
LDQM: U3.15; also elsewhere on the board
RAS#: U3.18; also elsewhere on the board
SD-CLK: X3.5 (CLK/SCLK); also elsewhere on the board
SD-CMD: R35.1, X3.3 (CMD/DIN); also elsewhere on the board
SD-DAT0: R34.1, X3.7 (DAT0/DOUT); also elsewhere on the board
SD-DAT1: R34.2 (1), X3.8 (DAT1/NC); also elsewhere on the board
SD-DAT2: R34.3 (1), X3.1 (DAT2/NC); also elsewhere on the board
SD-DAT3: R34.4 (1), X3.2 (DAT3_CD/CS#); also elsewhere on the board
SDRAM-CLK: U3.38; also elsewhere on the board
SDRAM-CS#: U3.19; also elsewhere on the board
UDQM: U3.39; also elsewhere on the board
VCC3V3: C3.2, C4.2, C5.2, C6.2, C7.2, C8.2, C9.2, C11.2, C12.2, C13.2, R2.2, R6.2, R7.2, R34.5 (2), R34.6 (2), R34.7 (2), R34.8 (2), R35.2, U3.1, U3.3, U3.9, U3.14, U3.27, U3.43, U3.49, U4.8, X3.4 (VDD); also elsewhere on the board
WE#: U3.16; also elsewhere on the board

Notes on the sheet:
U3 DECOUPLING -- each cap bridges one supply pin to the ground pin OPPOSITE it. In the 54-pin TSOP-II, pin n faces pin 55-n, and every supply pin faces a ground of its own domain: VDD 1/14/27 to VSS 54/41/28, VDDQ 3/9/43/49 to VSSQ 52/46/12/6. Alliance isolates VDDQ from VDD for DQ noise immunity -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
MASTER SPI BOOT (x4). M2:M1:M0 = 0:0:1 -- R20 pulls M0 to VCC3V3, R21/R22 pull M1/M2 to GND -- so at power-up the FPGA drives CCLK itself and clocks its bitstream out of U4 with no USB and no host present. That mode can only use the dedicated configuration pins: CCLK C11, FCS_B K19, D00_MOSI D18, D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
microSD runs the NATIVE 4-BIT SD BUS, not SPI. CLK, CMD and DAT0-DAT3 -- six signals, all in bank 34 byte group T0 (R2 T1 T2 U1 V2 W2), so they can be constrained as one bus. DAT1/DAT2 came from prototyping-header CHAN1/CHAN0; DAT3 is the old SPI chip-select, which needs no new pin. R34/R35 are the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
U3 = AS4C32M16SB-6TIN: 512Mbit (32M x 16) = 64MB. Pin-for-pin and dimensionally identical to the 256Mb AS4C16M16SA-6TIN it replaces -- all 54 pins and every TSOP-II dimension checked against both datasheets, and pin 40 is NC on both. ONE DIFFERENCE, AND IT IS NOT A PIN: the column address is A0-A9 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

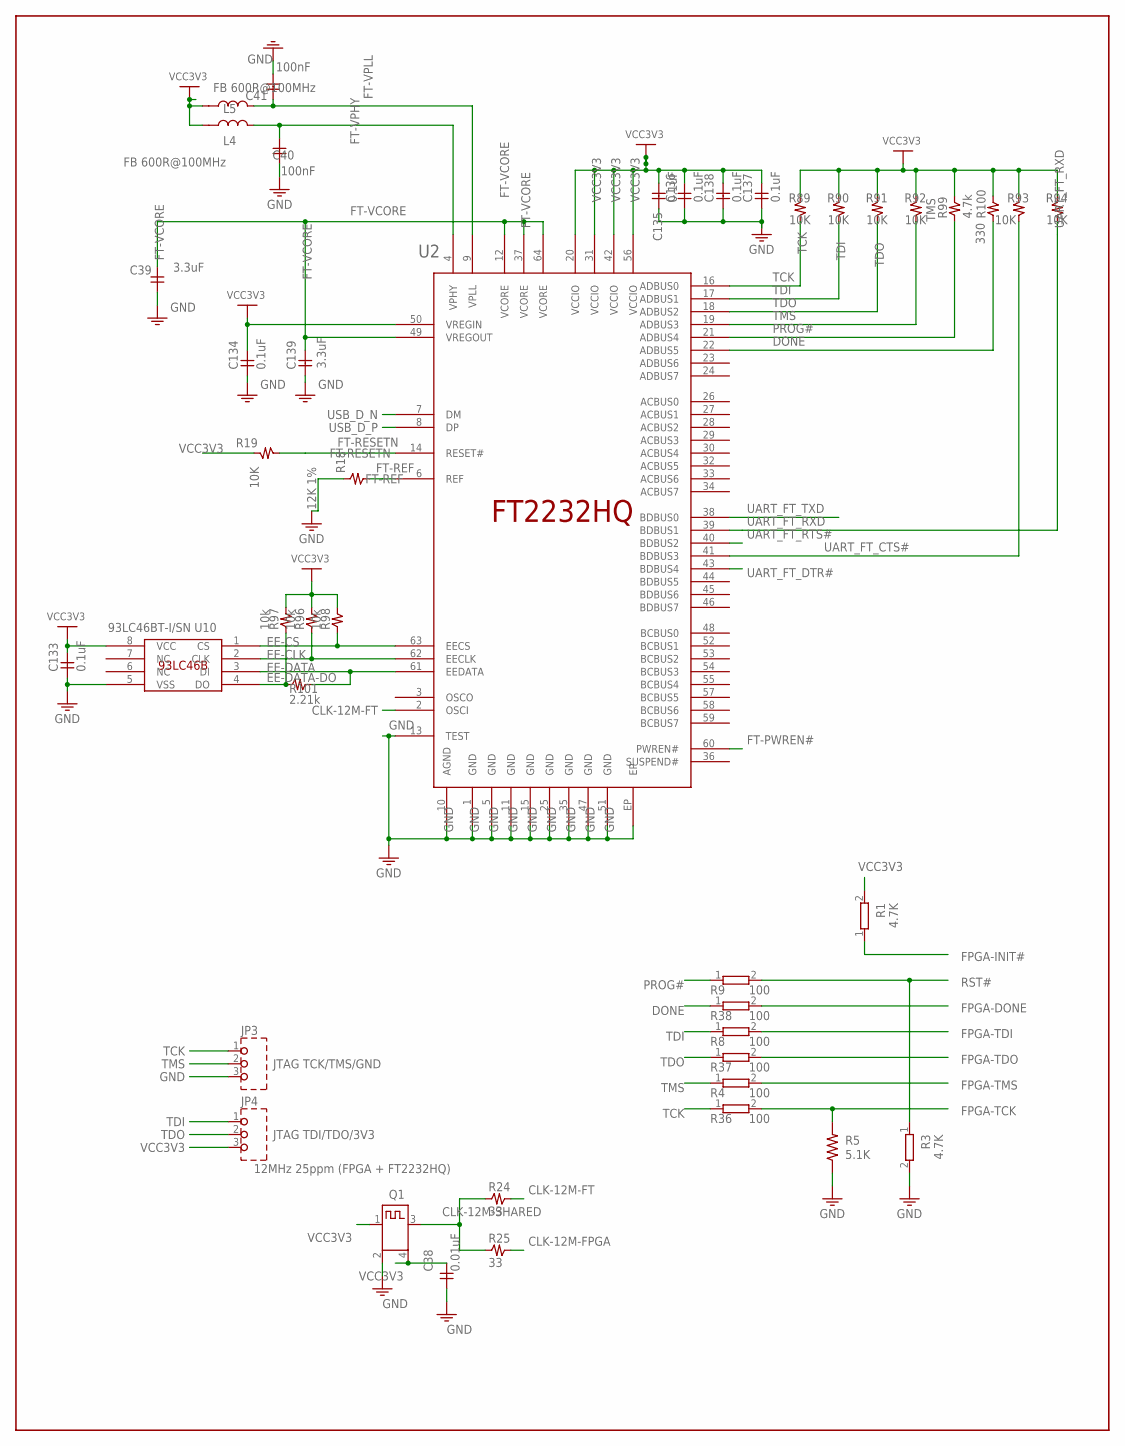
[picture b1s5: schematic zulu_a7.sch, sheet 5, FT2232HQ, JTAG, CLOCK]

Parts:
C38: 0.01uF; C0201
C39, C139: 3.3uF; C0402
C40, C41: 100nF; C0201
C133, C134, C135, C136, C137, C138: 0.1uF; C0201
JP3: JTAG TCK/TMS/GND; 1X03-NOSILK
JP4: JTAG TDI/TDO/3V3; 1X03-NOSILK
L4, L5: FB 600R@100MHz; IND0603
Q1: 12MHz 25ppm (FPGA + FT2232HQ); 32X25
R1, R3: 4.7K; R0201
R4, R8, R9, R36, R37, R38: 100; R0402
R5: 5.1K; R0201; MOUSER# 301-5.1K-RC
R18: 12K 1%; R0402
R19, R89, R90, R91, R92, R93, R94: 10K; R0201
R24, R25: 33; R0201
R96, R97, R98: 10k; R0201
R99: 4.7k; R0201
R100: 330; R0402
R101: 2.21k; R0201
U2: FT2232HQ USB-UART/JTAG Bridge; FT2232HQ-QFN64
U10: 93LC46BT-I/SN; SOIC8

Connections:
CLK-12M-FPGA: R25.2; also elsewhere on the board
CLK-12M-FT: R24.2, U2.2 (OSCI)
CLK-12M-SHARED: Q1.3, R24.1, R25.1
DONE: R38.1, R100.1, U2.22 (ADBUS5)
EE-CLK: R96.1, U2.62 (EECLK), U10.2 (CLK)
EE-CS: R98.1, U2.63 (EECS), U10.1 (CS)
EE-DATA: R101.2, U2.61 (EEDATA), U10.3 (DI)
EE-DATA-DO: R97.1, R101.1, U10.4 (DO)
FPGA-DONE: R38.2; also elsewhere on the board
FPGA-INIT#: R1.1; also elsewhere on the board
FPGA-TCK: R5.2, R36.2; also elsewhere on the board
FPGA-TDI: R8.2; also elsewhere on the board
FPGA-TDO: R37.2; also elsewhere on the board
FPGA-TMS: R4.2; also elsewhere on the board
FT-PWREN#: U2.60 (PWREN#); also elsewhere on the board
FT-REF: R18.2, U2.6 (REF)
FT-RESETN: R19.1, U2.14 (RESET#)
FT-VCORE: C39.2, C139.2, U2.12 (VCORE), U2.37 (VCORE), U2.49 (VREGOUT), U2.64 (VCORE)
FT-VPHY: C40.2, L4.1, U2.4 (VPHY)
FT-VPLL: C41.2, L5.1, U2.9 (VPLL)
GND: C38.1, C39.1, C40.1, C41.1, C133.1, C134.1, C135.1, C136.1, C137.1, C138.1, C139.1, JP3.3, Q1.2, R3.2, R5.1, R18.1, U2.1 (GND), U2.5 (GND), U2.10 (AGND), U2.11 (GND), U2.13 (TEST), U2.15 (GND), U2.25 (GND), U2.35 (GND), U2.47 (GND), U2.51 (GND), U2.EP, U10.5 (VSS); also elsewhere on the board
PROG#: R9.1, R99.1, U2.21 (ADBUS4)
RST#: R3.1, R9.2; also elsewhere on the board
TCK: JP3.1, R36.1, R89.1, U2.16 (ADBUS0)
TDI: JP4.1, R8.1, R90.1, U2.17 (ADBUS1)
TDO: JP4.2, R37.1, R91.1, U2.18 (ADBUS2)
TMS: JP3.2, R4.1, R92.1, U2.19 (ADBUS3)
UART_FT_CTS#: R93.1, U2.41 (BDBUS3); also elsewhere on the board
UART_FT_DTR#: U2.43 (BDBUS4); also elsewhere on the board
UART_FT_RTS#: U2.40 (BDBUS2); also elsewhere on the board
UART_FT_RXD: R94.1, U2.39 (BDBUS1); also elsewhere on the board
UART_FT_TXD: U2.38 (BDBUS0); also elsewhere on the board
USB_D_N: U2.7 (DM); also elsewhere on the board
USB_D_P: U2.8 (DP); also elsewhere on the board
VCC3V3: C38.2, C133.2, C134.2, C135.2, C136.2, C137.2, C138.2, JP4.3, L4.2, L5.2, Q1.1, Q1.4, R1.2, R19.2, R89.2, R90.2, R91.2, R92.2, R93.2, R94.2, R96.2, R97.2, R98.2, R99.2, R100.2, U2.20 (VCCIO), U2.31 (VCCIO), U2.42 (VCCIO), U2.50 (VREGIN), U2.56 (VCCIO), U10.8 (VCC); also elsewhere on the board
